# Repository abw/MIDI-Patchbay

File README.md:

# MIDI-Patchbay
This project contains hardware and firmware for a 4x4 MIDI
merger/splitter patchbay based on an Arduino MEGA 2560.
It has 4 MIDI inputs and 4 MIDI outputs.  In the
simplest case, it will merge all 4 inputs and then split the combined
MIDI stream across the 4 outputs.  However the routing is controlled by
the firmware so you can configure it to patch any combination of inputs
into any of the outputs.

# Table of contents
* [Hardware](#hardware)
* [Firmware](#firmware)
* [Warning](#warning)

## Hardware:

The [hardware](hardware)
directory contains Eagle schematics, board designs and Gerber files for
the following modules.

* [MIDI-Patchbay-Shield](hardware/MIDI-Patchbay-Shield)
is a shield for an Arduino MEGA 2560 that provides 4 MIDI inputs, 4 MIDI
outputs and connectors for interfacing to the
[MIDI-Patchbay-Display](hardware/MIDI-Patchbay-Display)
board.  It also contains connectors for accessing 8 analog pins and 8
digital pins for further expansion.  This is the main board that you
need to build.

* [MIDI-Patchbay-Display](hardware/MIDI-Patchbay-Display)
is a board for mounting a 16x2 LCD display and two RGB rotary encoders.
This is an optional extra.  You can build a fully functioning MIDI
merger/splitter without it.

* [MIDI-Patchbay-Simple](hardware/MIDI-Patchbay-Simple)
is the predecessor of the [MIDI-Patchbay-Shield](hardware/MIDI-Patchbay-Shield).
This is a reduced size shield for the Arduino MEGA 2560 that only has 4
MIDI inputs and 4 MIDI outputs, along with the relevant circuitry to
support it.  If you just want a simple MIDI merger/splitter without any
extra frills then this is the simplest option as an *alternative* to the
above.

The boards use surface mount (SMD) components, but nothing smaller than
0805 (that's 2012 in metric: approximately 2.0mm x 1.25mm) which can easily
be soldered by hand.  It's really not much harder than through-hole
components, so don't be put off if you haven't used SMD before.  But you
will need to invest in some tweezers and a magnifier/light unit to help
you see what you're doing.  And of course, a decent soldering iron.

## Firmware:

The [firmware](firmware)
directory contains the source code for the firmware that powers the
boards listed above.  It is built around the Arduino [MIDI Library](https://github.com/FortySevenEffects/arduino_midi_library)
by [Forty Seven Effects](https://github.com/FortySevenEffects).

* [MIDI-Patchbay-Simple.ino](firmware/MIDI-Patchbay-Simple.ino) implements
a simple 4x4 MIDI patchbay that merges all four MIDI inputs and duplicates
them across all four MIDI outputs.  It is specifically for use with the
basic [MIDI-Patchbay-Simple](hardware/MIDI-Patchbay-Simple) board, but
can also be used with the more advanced [MIDI-Patchbay-Shield](hardware/MIDI-Patchbay-Shield)
if you just need simple functionality.  Or you can use this as a starting
point for your own implementation of the firmware.

## Warning:

These are new designs that haven't been fully tested yet.  Use them at
your own risk.

## Author

Andy Wardley <abw@wardley.org> December 2017

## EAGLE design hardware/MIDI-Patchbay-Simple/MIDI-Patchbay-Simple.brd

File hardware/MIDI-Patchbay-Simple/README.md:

# MIDI-Patchbay-Simple

This directory contains the schematic and board layout for the
predecessor/prototype of the [MIDI Patchbay Shield](../MIDI-Patchbay-Shield) for the Arduino MEGA 2560.

This is a simple 4 MIDI IN / 4 MIDI OUT merger and splitter.

The [MIDI Patchbay Shield](../MIDI-Patchbay-Shield)
is the newer design with more functionality, but if you want something
simple and slightly easier/cheaper/quicker to build then this might be
the droids you're looking for.

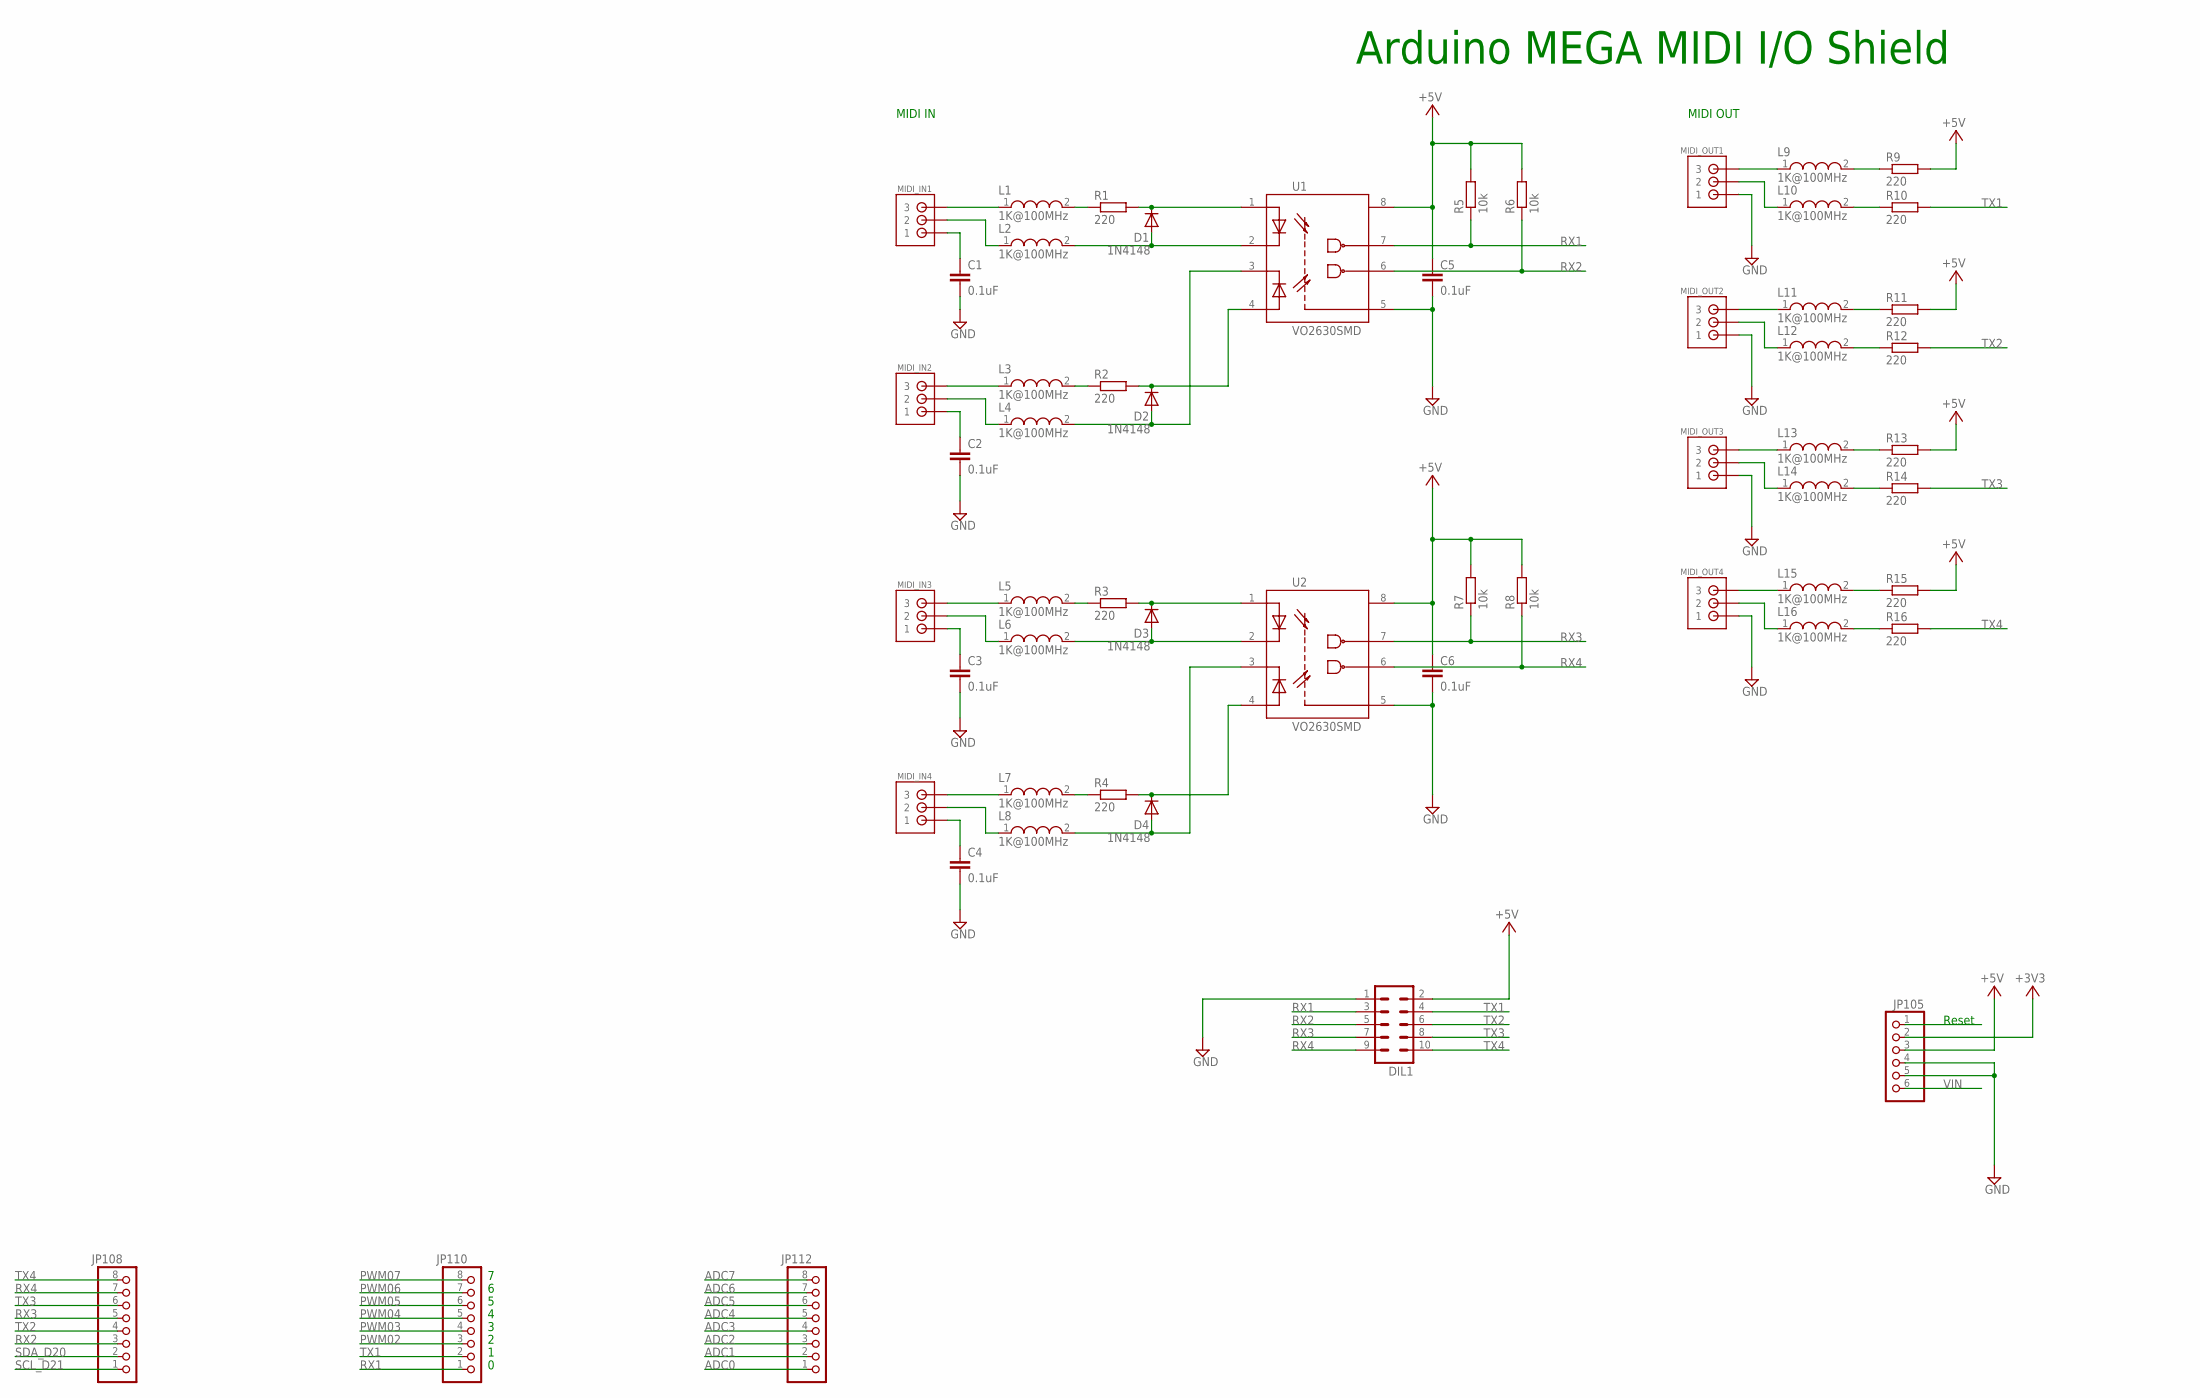
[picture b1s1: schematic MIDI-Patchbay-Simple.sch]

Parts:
C1, C2, C3, C4: 0.1uF; 0805
C5, C6: 0.1uF; C0805
D1, D2, D3, D4: 1N4148; SOD323-W
DIL1: ML10
JP105: PINHD-1X6; 1X06
JP108, JP110, JP112: PINHD-1X8; 1X08
L1, L2, L3, L4, L5, L6, L7, L8, L9, L10, L11, L12, L13, L14, L15, L16: 1K@100MHz; WE-RFI_0805
MIDI_IN1, MIDI_IN2, MIDI_IN3, MIDI_IN4: JST-XA-03-PIN; JST-XA-03
MIDI_OUT1, MIDI_OUT2, MIDI_OUT3, MIDI_OUT4: JST-XA-03-PIN; JST-XA-03
R1, R2, R3, R4, R9, R10, R11, R12, R13, R14, R15, R16: 220; M0805
R5, R6, R7, R8: 10k; R0805
U1, U2: VO2630SMD; SOIC254P1030X390-8N

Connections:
+3V3: JP105.2
+5V: C5.1, C6.1, DIL1.2, JP105.3, R5.2, R6.2, R7.2, R8.2, R9.2, R11.2, R13.2, R15.2, U1.8 (VCC), U2.8 (VCC)
ADC0: JP112.1
ADC1: JP112.2
ADC2: JP112.3
ADC3: JP112.4
ADC4: JP112.5
ADC5: JP112.6
ADC6: JP112.7
ADC7: JP112.8
GND: C1.2, C2.2, C3.2, C4.2, C5.2, C6.2, DIL1.1, JP105.4, JP105.5, MIDI_OUT1.1, MIDI_OUT2.1, MIDI_OUT3.1, MIDI_OUT4.1, U1.5 (GND), U2.5 (GND)
IC1: D1.C, R1.2, U1.1 (A1)
IC2: D2.C, R2.2, U1.4 (A2)
IC3: D3.C, R3.2, U2.1 (A1)
IC4: D4.C, R4.2, U2.4 (A2)
unnamed: L1.1, MIDI_IN1.3
unnamed: L2.1, MIDI_IN1.2
unnamed: C1.1, MIDI_IN1.1
unnamed: L1.2, R1.1
unnamed: L9.1, MIDI_OUT1.3
unnamed: D1.A, L2.2, U1.2 (C1)
unnamed: L10.1, MIDI_OUT1.2
unnamed: L9.2, R9.1
unnamed: L10.2, R10.1
unnamed: L3.1, MIDI_IN2.3
unnamed: L4.1, MIDI_IN2.2
unnamed: L3.2, R2.1
unnamed: D2.A, L4.2, U1.3 (C2)
unnamed: C2.1, MIDI_IN2.1
unnamed: L5.1, MIDI_IN3.3
unnamed: L6.1, MIDI_IN3.2
unnamed: L5.2, R3.1
unnamed: D3.A, L6.2, U2.2 (C1)
unnamed: C3.1, MIDI_IN3.1
unnamed: L7.1, MIDI_IN4.3
unnamed: L8.1, MIDI_IN4.2
unnamed: L7.2, R4.1
unnamed: D4.A, L8.2, U2.3 (C2)
unnamed: C4.1, MIDI_IN4.1
unnamed: L11.1, MIDI_OUT2.3
unnamed: L12.1, MIDI_OUT2.2
unnamed: L11.2, R11.1
unnamed: L12.2, R12.1
unnamed: L13.1, MIDI_OUT3.3
unnamed: L14.1, MIDI_OUT3.2
unnamed: L13.2, R13.1
unnamed: L14.2, R14.1
unnamed: L15.1, MIDI_OUT4.3
unnamed: L16.1, MIDI_OUT4.2
unnamed: L15.2, R15.1
unnamed: L16.2, R16.1
PWM02: JP110.3
PWM03: JP110.4
PWM04: JP110.5
PWM05: JP110.6
PWM06: JP110.7
PWM07: JP110.8
RESET: JP105.1
RX1: DIL1.3, JP110.1, R5.1, U1.7 (VO1)
RX2: DIL1.5, JP108.3, R6.1, U1.6 (VO2)
RX3: DIL1.7, JP108.5, R7.1, U2.7 (VO1)
RX4: DIL1.9, JP108.7, R8.1, U2.6 (VO2)
SCL_D21: JP108.1
SDA_D20: JP108.2
TX1: DIL1.4, JP110.2, R10.2
TX2: DIL1.6, JP108.4, R12.2
TX3: DIL1.8, JP108.6, R14.2
TX4: DIL1.10, JP108.8, R16.2
VIN: JP105.6

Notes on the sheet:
Arduino MEGA MIDI I/O Shield
Reset
MIDI IN
MIDI OUT

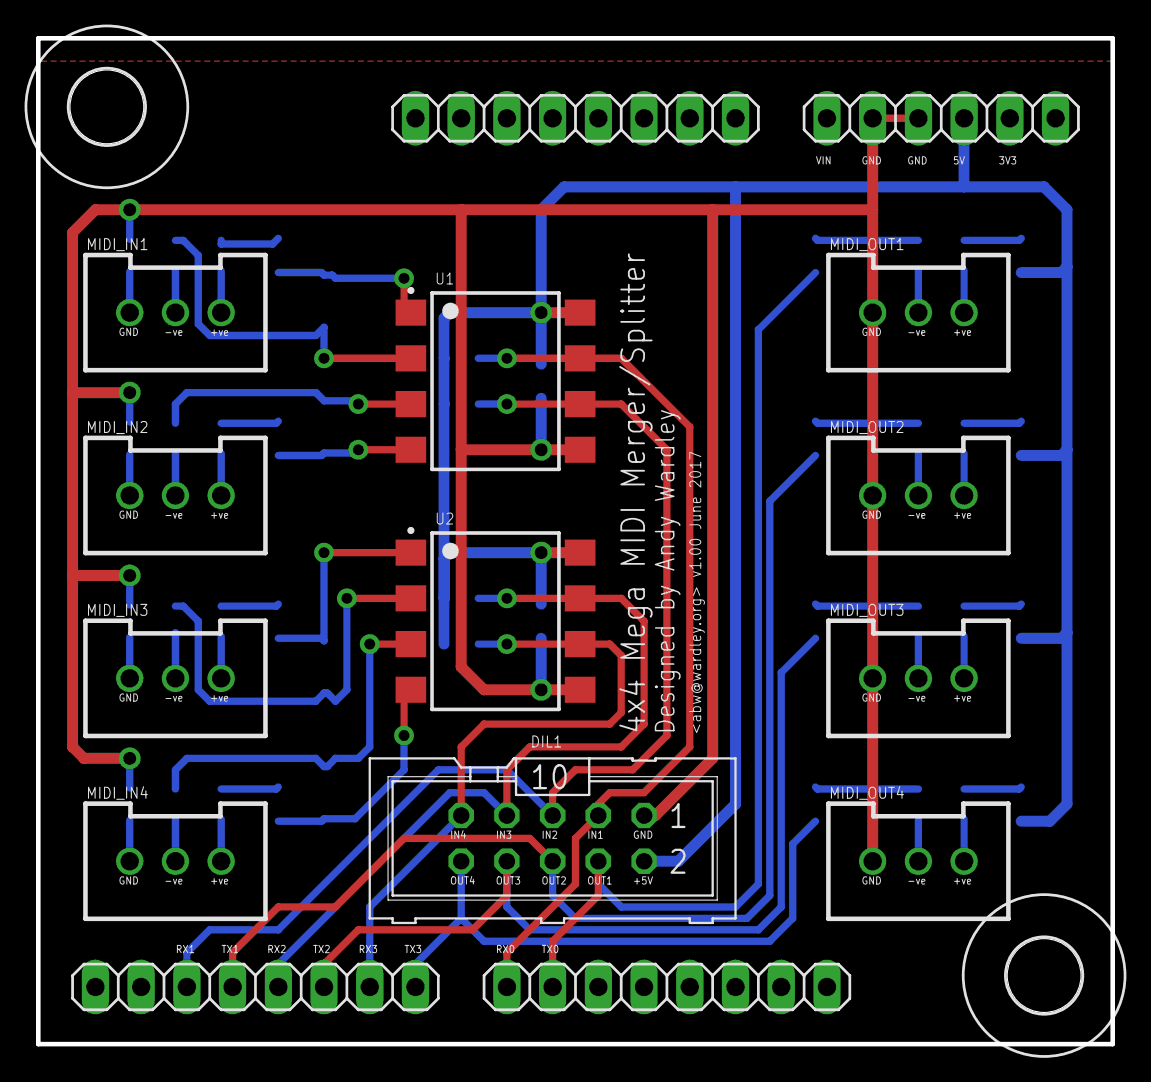
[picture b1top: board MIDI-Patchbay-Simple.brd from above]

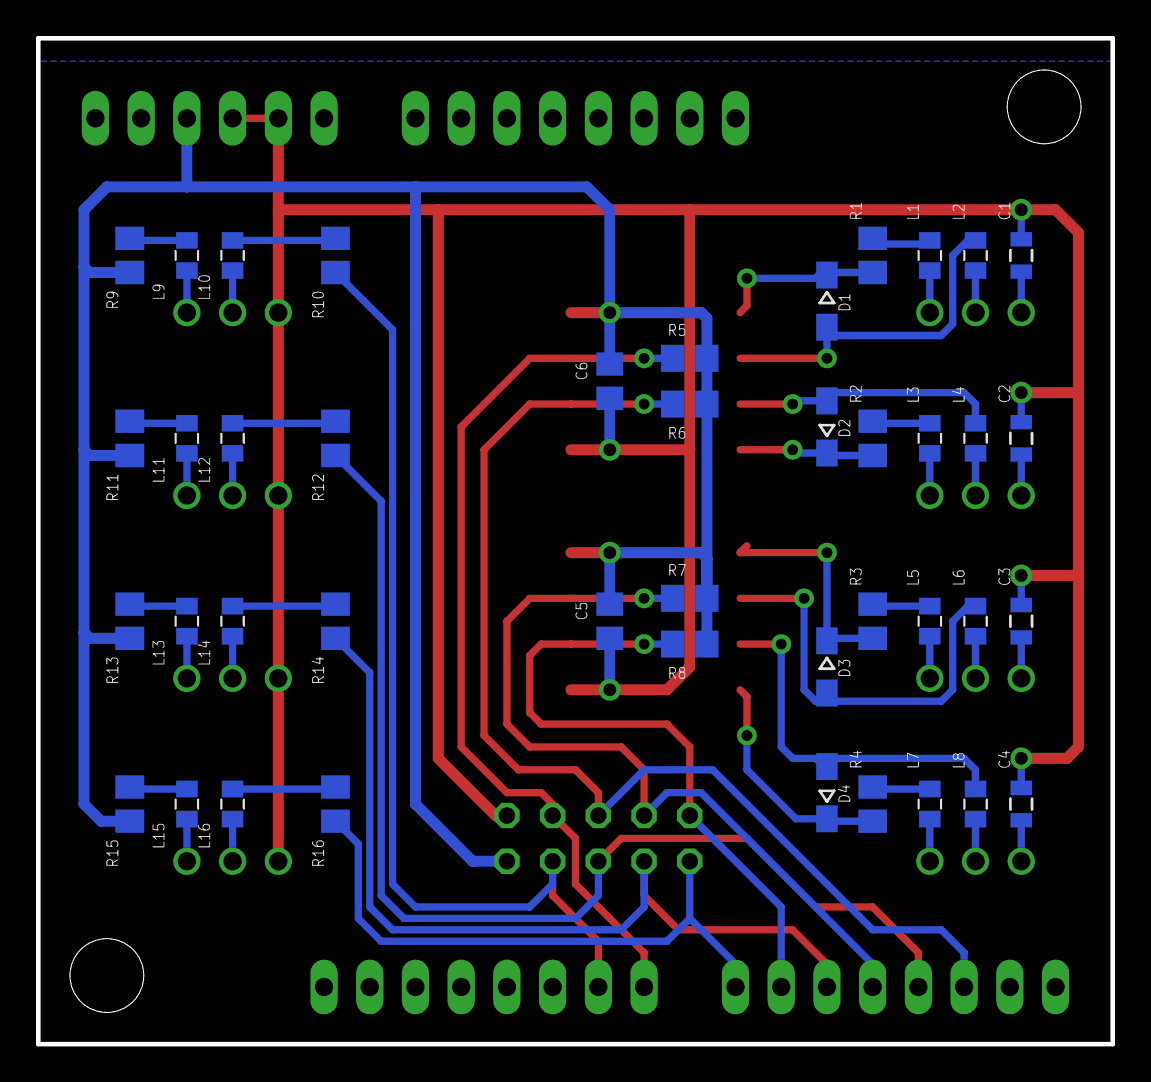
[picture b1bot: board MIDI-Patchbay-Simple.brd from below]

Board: 2 copper layers, 59.7 x 55.9 mm, 59 parts (42 on the bottom side), 50 nets.

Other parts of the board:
U$1, U$2: 4,1

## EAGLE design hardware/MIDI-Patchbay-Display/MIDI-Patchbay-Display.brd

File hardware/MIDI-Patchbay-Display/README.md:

# MIDI-Patchbay-Display

This directory contains the schematic and board layout for a daughter
board for mounting a 16x2 LCD display and 2 [RGB rotary encoders](https://www.sparkfun.com/products/10982).

This is an optional extra that can be used in conjunction with the
[MIDI-Patchbay-Shield](../MIDI-Patchbay-Shield)
or with your own projects that require an LCD display and/or encoders.

A 10 pin (2x5) IDC connector is used to connect to the LCD.  A 16 pin
(2x8) IDC connector is used to connect to the rotary encoders.

The board contains the "anti-chatter" circuits on the rotaty encoders that
are recommended in the [data sheet](https://cdn.sparkfun.com/datasheets/Components/Switches/EC12PLRGBSDVBF-D-25K-24-24C-6108-6HSPEC.pdf).
It also has a pull-down resistor, current limiting resistor and debounce
capacitor on the push switches for each encoder.

The RGB LEDs in the encoders, and the LED in the backlight of the LCD,
are all switched through transistors with the appropriate
current-limiting resistors in series.  The intensity of the LEDs can
be changed using Pulse Width Modulation (PWM) directly from Arduino
pins.  The transistors are used so that we're not powering the LEDs
directly from the Arduino pins and don't have to worry about exceeding
any of the current source/sink limits of the microprocessor.

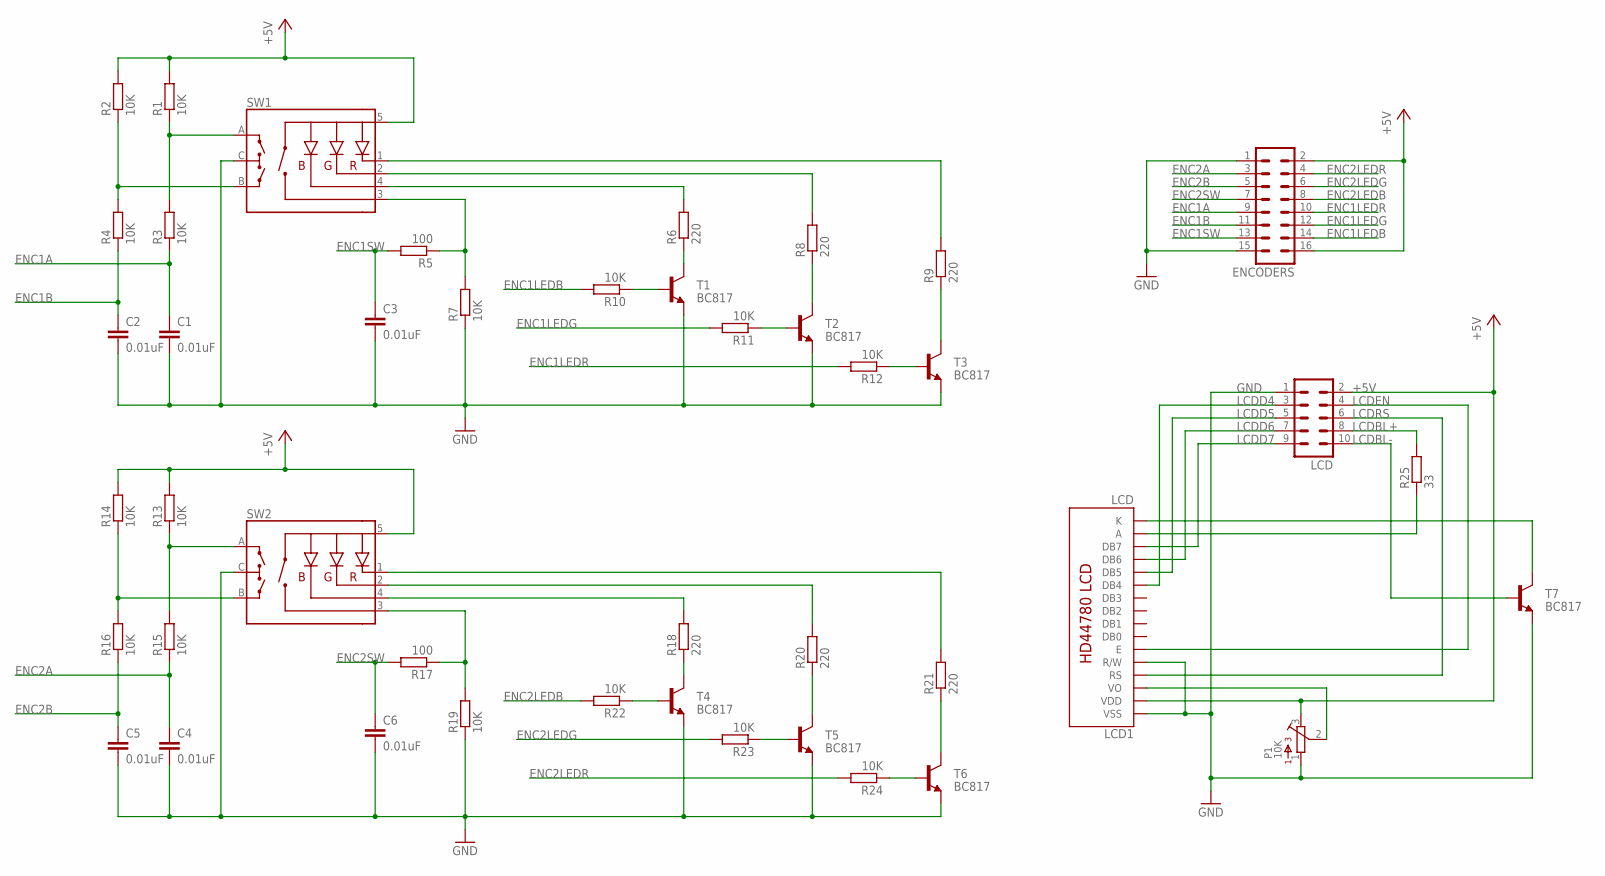
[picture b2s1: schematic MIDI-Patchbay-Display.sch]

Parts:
C1, C2, C3, C4, C5, C6: 0.01uF; 0805
ENCODERS: ML16
LCD: ML10
LCD1: LCD; LCD-16X2-4HOLES
P1: 10K; 3386W
R1, R2, R3, R4, R7, R10, R11, R12, R13, R14, R15, R16, R19, R22, R23, R24: 10K; R0805
R5, R17: 100; R0805
R6, R8, R9, R18, R20, R21: 220; R0805
R25: 33; R0805
SW1, SW2: ENCODER_RGB_CA; ENCODER_LED_3
T1, T2, T3, T4, T5, T6, T7: BC817; SOT23

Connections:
+5V: ENCODERS.2, ENCODERS.16, LCD.2, LCD1.2 (VDD), P1.3, R1.2, R2.2, R13.2, R14.2, SW1.5 (+), SW2.5 (+)
ENC1A: C1.1, ENCODERS.9, R3.1
ENC1APIN: R1.1, R3.2, SW1.A
ENC1B: C2.1, ENCODERS.11, R4.1
ENC1BPIN: R2.1, R4.2, SW1.B
ENC1LEDB: ENCODERS.14, R10.2
ENC1LEDG: ENCODERS.12, R11.2
ENC1LEDR: ENCODERS.10, R12.2
ENC1SW: C3.1, ENCODERS.13, R5.2
ENC2A: C4.1, ENCODERS.3, R15.1
ENC2APIN: R13.1, R15.2, SW2.A
ENC2B: C5.1, ENCODERS.5, R16.1
ENC2BPIN: R14.1, R16.2, SW2.B
ENC2LEDB: ENCODERS.8, R22.2
ENC2LEDG: ENCODERS.6, R23.2
ENC2LEDR: ENCODERS.4, R24.2
ENC2SW: C6.1, ENCODERS.7, R17.2
GND: C1.2, C2.2, C3.2, C4.2, C5.2, C6.2, ENCODERS.1, ENCODERS.15, LCD.1, LCD1.1 (VSS), LCD1.5 (R/W), P1.1, R7.1, R19.1, SW1.C, SW2.C, T1.2 (E), T2.2 (E), T3.2 (E), T4.2 (E), T5.2 (E), T6.2 (E), T7.2 (E)
LCDA: LCD1.15 (A), R25.1
LCDBL+: LCD.8, R25.2
LCDBL-: LCD.10, T7.1 (B)
LCDD4: LCD.3, LCD1.11 (DB4)
LCDD5: LCD.5, LCD1.12 (DB5)
LCDD6: LCD.7, LCD1.13 (DB6)
LCDD7: LCD.9, LCD1.14 (DB7)
LCDEN: LCD.4, LCD1.6 (E)
LCDK: LCD1.16 (K), T7.3 (C)
LCDRS: LCD.6, LCD1.4 (RS)
unnamed: R6.1, T1.3 (C)
unnamed: R6.2, SW1.4 (-B)
unnamed: LCD1.3 (VO), P1.2
unnamed: R8.1, T2.3 (C)
unnamed: R10.1, T1.1 (B)
unnamed: R11.1, T2.1 (B)
unnamed: R8.2, SW1.2 (-G)
unnamed: R9.1, T3.3 (C)
unnamed: R12.1, T3.1 (B)
unnamed: R9.2, SW1.1 (-R)
unnamed: R5.1, R7.2, SW1.3 (SW)
unnamed: R18.2, SW2.4 (-B)
unnamed: R18.1, T4.3 (C)
unnamed: R22.1, T4.1 (B)
unnamed: R20.1, T5.3 (C)
unnamed: R23.1, T5.1 (B)
unnamed: R20.2, SW2.2 (-G)
unnamed: R21.1, T6.3 (C)
unnamed: R24.1, T6.1 (B)
unnamed: R21.2, SW2.1 (-R)
unnamed: R17.1, R19.2, SW2.3 (SW)

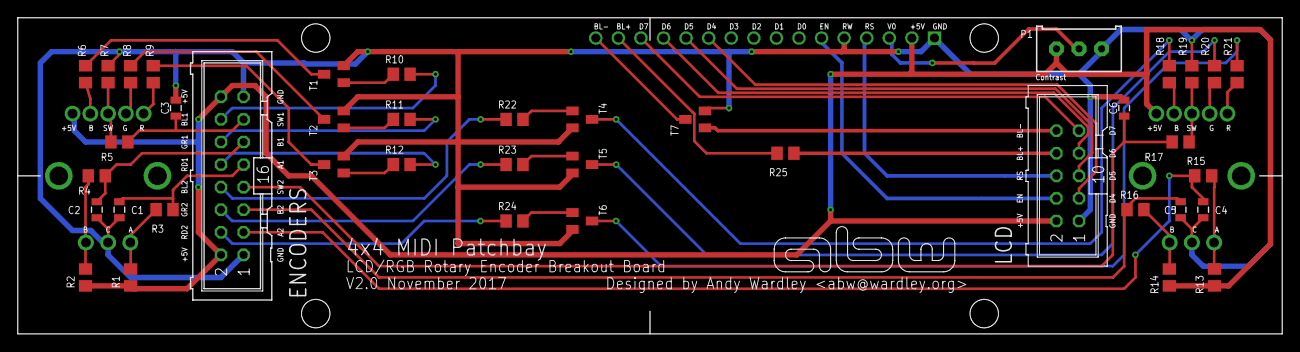
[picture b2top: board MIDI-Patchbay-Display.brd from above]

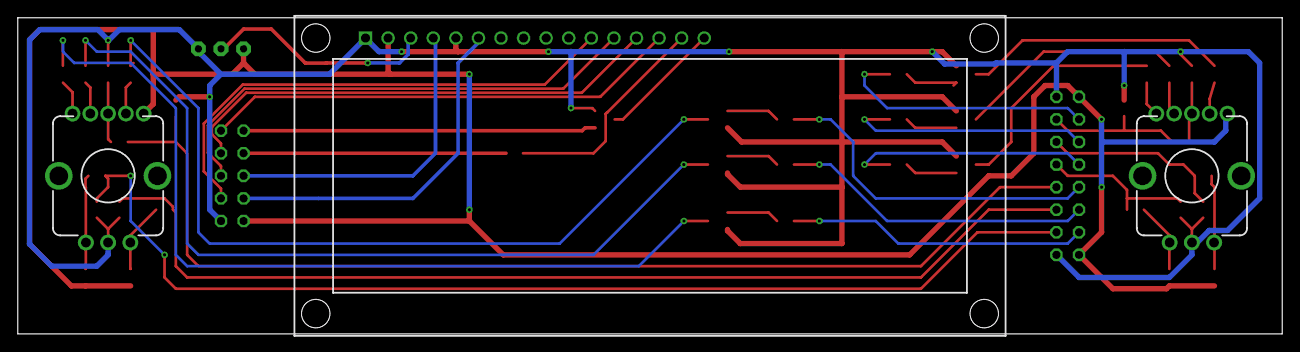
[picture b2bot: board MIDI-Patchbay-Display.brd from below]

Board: 2 copper layers, 142.2 x 35.6 mm, 45 parts (3 on the bottom side), 49 nets.

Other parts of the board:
U$1: ABWLOGO-MICRO

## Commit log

2017-12-01 Added hardware designs and updated README
2017-12-01 Added MIDI-Patchbay-Simple
2017-12-01 Added more README files
2017-12-01 More README
2017-12-01 More README updates
2017-12-01 README updates
2017-12-01 Added images for boards and schematics
2017-12-01 Added gerber files
2017-12-01 Added firmware for simple 4x4 patchbay
2017-12-01 Added firmware README
2017-12-01 Added more firmware
2017-12-01 Comment tweak
2017-12-01 Added new tests for LCD, encoders and panic/power switch LEDs
2017-12-02 Misc changes in tests
2017-12-02 Added first version of main firmware
2017-12-02 Updated panic flash
2017-12-07 Added menus directory
2017-12-07 Firmware development
2017-12-07 Added .gitignore
2017-12-07 Added oscillators and start of patches
2017-12-08 Replaced C++ classes with smaller, simpler C functions and structs
2017-12-08 Added test program to .gitignore

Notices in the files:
parts and their libraries:
EagleLibrary_Wuerth_Elektronik_eiSos_rev: Copyright: Würth Elektronik
SparkFun-Capacitors: Licensing: Creative Commons ShareAlike 4.0 International - https://creativecommons.org/licenses/by-sa/4.0
